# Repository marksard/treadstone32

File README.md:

# treadstone32
A 32-key compact keyboard project.  

This repository contains projects from rev2 onward. rev1, lite related projects can be found at the following links.  
[https://github.com/marksard/Keyboards/tree/master](https://github.com/marksard/Keyboards/tree/master)

# Completed example

# Layout

# Support software

QMK Firmware  
https://github.com/marksard/qmk_firmware/tree/own_build/keyboards/marksard/treadstone32/rev2

# Build guide

https://github.com/marksard/treadstone32/blob/main/documents/buildguide.md

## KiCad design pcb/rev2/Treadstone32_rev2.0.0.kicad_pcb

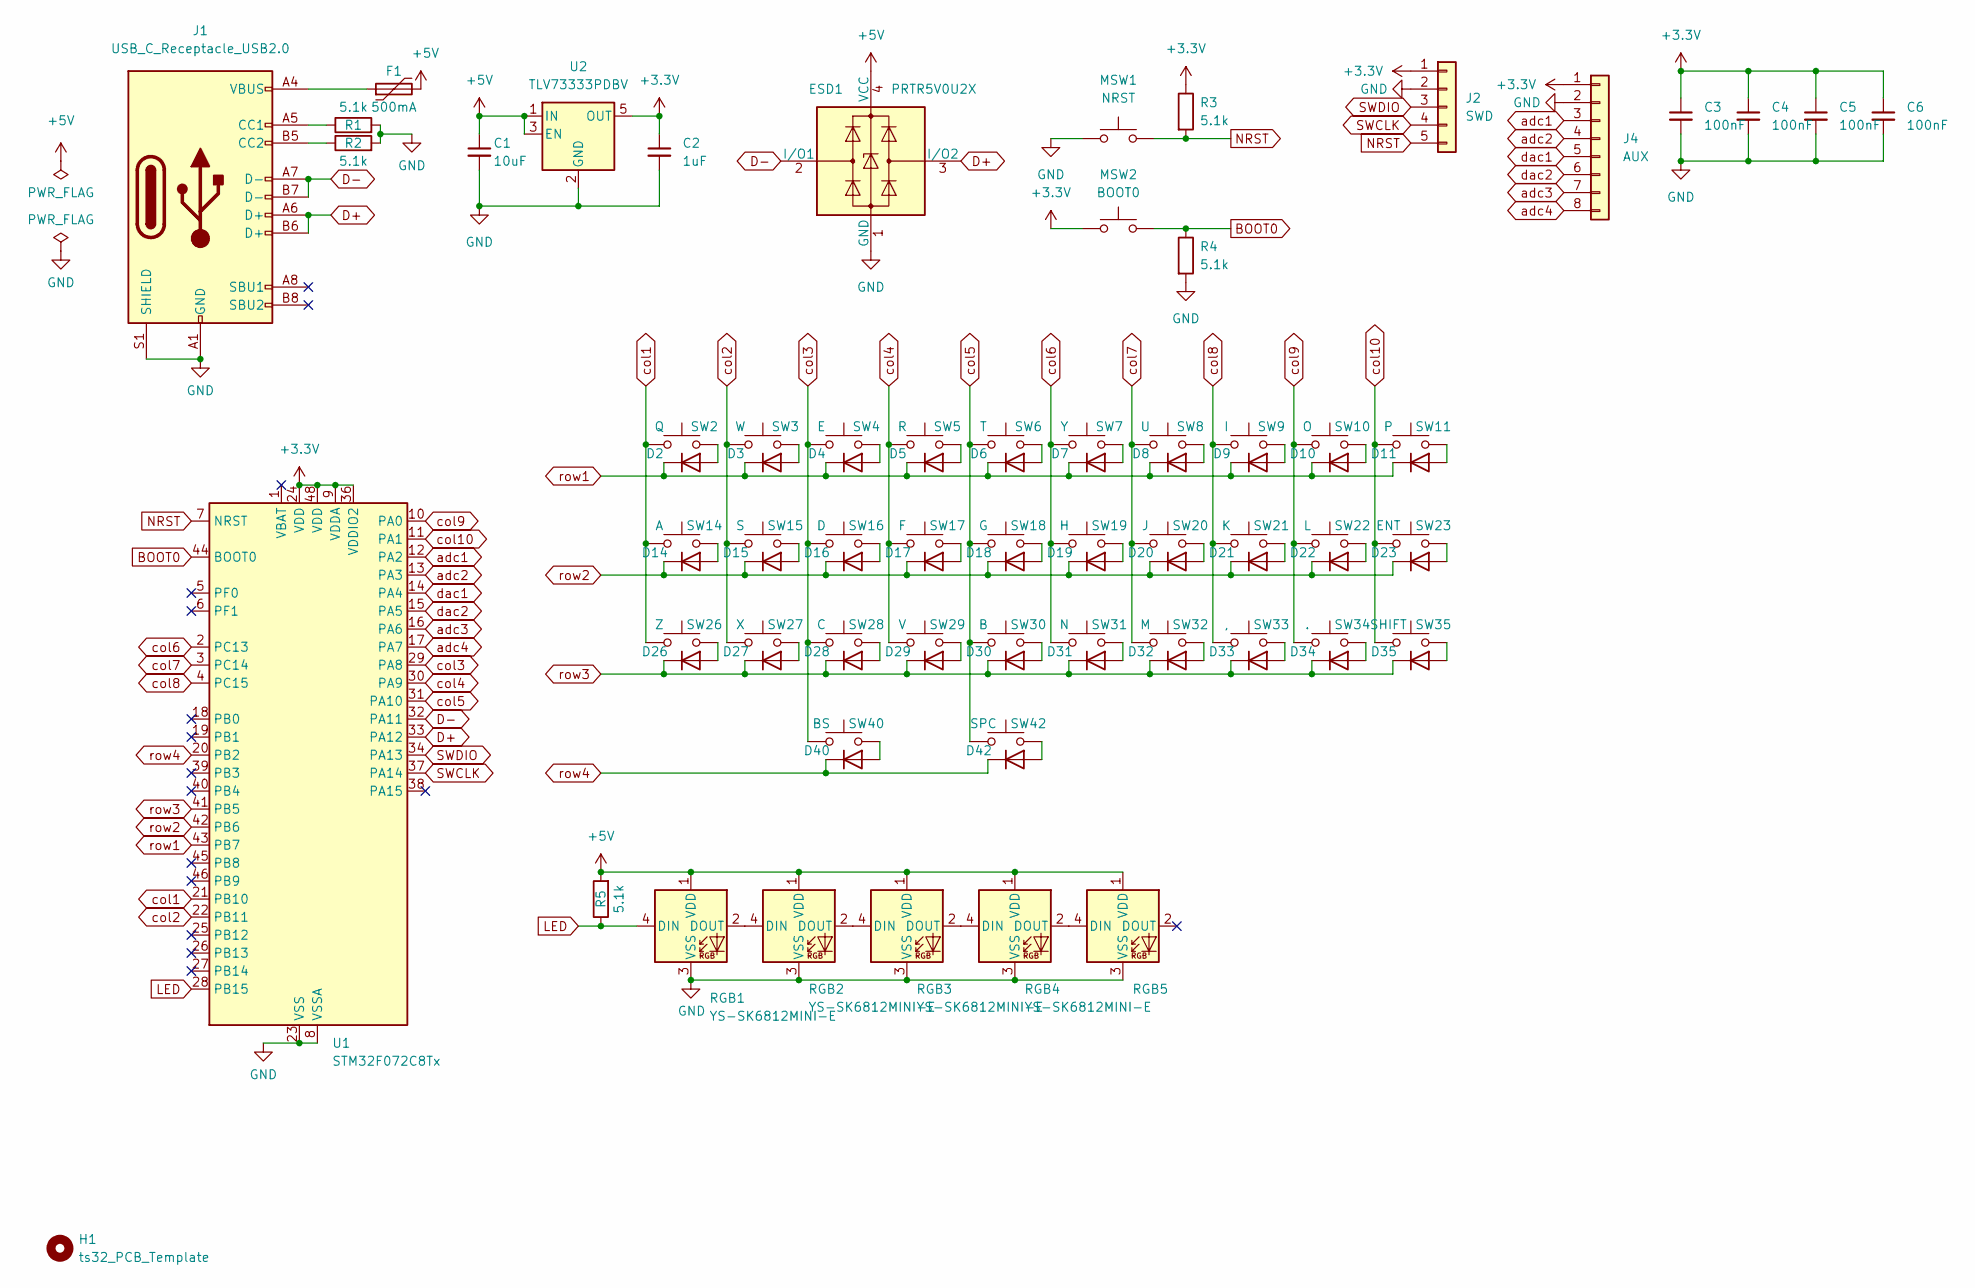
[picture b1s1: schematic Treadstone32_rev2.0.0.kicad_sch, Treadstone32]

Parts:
C1: 10uF; C_0603_1608Metric; LCSC C19702
C2: 1uF; C_0402_1005Metric; LCSC C52923
C3, C4, C5, C6: 100nF; C_0402_1005Metric; LCSC C1525
D2, D3, D4, D5, D6, D7, D8, D9, D10, D11, D14, D15, D16, D17, D18, D19, D20, D21, D22, D23, D26, D27, D28, D29, D30, D31, D32, D33, D34, D35, D40, D42: D; D_SOD-123; LCSC C81598
ESD1: PRTR5V0U2X; SOT-143; LCSC C12333
F1: 500mA; Fuse_0805_2012Metric; LCSC C261942
H1: ts32_PCB_Template; ts32_PCB_Template_v2.0.0
J1: USB_C_Receptacle_USB2.0; HRO-TYPE-C-31-M-13x; LCSC C2848619
J2: SWD; PinHeader_1x05_P2.54mm_Vertical
J4: AUX; PinHeader_1x08_P2.54mm_Vertical
MSW1: NRST; TVBP06-B043CB
MSW2: BOOT0; TVBP06-B043CB
R1, R2: 5.1k; R_0603_1608Metric; LCSC C23186
R3, R4: 5.1k; R_0402_1005Metric; LCSC C23186
R5: 5.1k; R_0603_1608Metric; LCSC C445832
RGB1, RGB2, RGB3, RGB4, RGB5: YS-SK6812MINI-E; YS-SK6812MINI-E_undergrow; LCSC C5378731
SW2: Q; MX-Hotswap-1U_F; LCSC C5156480
SW3: W; MX-Hotswap-1U_F; LCSC C5156480
SW4: E; MX-Hotswap-1U_F; LCSC C5156480
SW5: R; MX-Hotswap-1U_F; LCSC C5156480
SW6: T; MX-Hotswap-1U_F; LCSC C5156480
SW7: Y; MX-Hotswap-1U_F; LCSC C5156480
SW8: U; MX-Hotswap-1U_F; LCSC C5156480
SW9: I; MX-Hotswap-1U_F; LCSC C5156480
SW10: O; MX-Hotswap-1U_F; LCSC C5156480
SW11: P; MX-Hotswap-1U_F; LCSC C5156480
SW14: A; MX-Hotswap-1U_F; LCSC C5156480
SW15: S; MX-Hotswap-1U_F; LCSC C5156480
SW16: D; MX-Hotswap-1U_F; LCSC C5156480
SW17: F; MX-Hotswap-1U_F; LCSC C5156480
SW18: G; MX-Hotswap-1U_F; LCSC C5156480
SW19: H; MX-Hotswap-1U_F; LCSC C5156480
SW20: J; MX-Hotswap-1U_F; LCSC C5156480
SW21: K; MX-Hotswap-1U_F; LCSC C5156480
SW22: L; MX-Hotswap-1U_F; LCSC C5156480
SW23: ENT; MX-Hotswap-1U_F; LCSC C5156480
SW26: Z; MX-Hotswap-1U_F; LCSC C5156480
SW27: X; MX-Hotswap-1U_F; LCSC C5156480
SW28: C; MX-Hotswap-1U_F; LCSC C5156480
SW29: V; MX-Hotswap-1U_F; LCSC C5156480
SW30: B; MX-Hotswap-1U_F; LCSC C5156480
SW31: N; MX-Hotswap-1U_F; LCSC C5156480
SW32: M; MX-Hotswap-1U_F; LCSC C5156480
SW33: ,; MX-Hotswap-1U_F; LCSC C5156480
SW34: .; MX-Hotswap-1U_F; LCSC C5156480
SW35: SHIFT; MX-Hotswap-1U_F; LCSC C5156480
SW40: BS; MX-Hotswap-1U_F; LCSC C5156480
SW42: SPC; MX-Hotswap-1U_F; LCSC C5156480
U1: STM32F072C8Tx; LQFP-48_7x7mm_P0.5mm; LCSC C80488
U2: TLV73333PDBV; SOT-23-5; LCSC C134139

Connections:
+3.3V: C2.1, C3.1, C4.1, C5.1, C6.1, J2.1, J4.1, MSW2.1, R3.1, U1.9 (VDDA), U1.24 (VDD), U1.36 (VDDIO2), U1.48 (VDD), U2.5 (OUT)
+5V: C1.1, ESD1.4 (VCC), F1.2, R5.2, U2.1 (IN), U2.3 (EN); also elsewhere on the board
BOOT0: MSW2.2, R4.1, U1.44 (BOOT0)
D+: ESD1.3 (I/O2), J1.A6 (D+), J1.B6 (D+), U1.33 (PA12)
D-: ESD1.2 (I/O1), J1.A7 (D-), J1.B7 (D-), U1.32 (PA11)
GND: C1.2, C2.2, C3.2, C4.2, C5.2, C6.2, ESD1.1 (GND), J1.A1 (GND), J1.A12 (GND), J1.B1 (GND), J1.B12 (GND), J1.S1 (SHIELD), J2.2, J4.2, MSW1.1, R1.2, R2.2, R4.2, U1.8 (VSSA), U1.23 (VSS), U1.35 (VSS), U1.47 (VSS), U2.2 (GND); also elsewhere on the board
LED: R5.1, U1.28 (PB15); also elsewhere on the board
NRST: J2.5, MSW1.2, R3.2, U1.7 (NRST)
unnamed: D2.2 (A), SW2.2
unnamed: D3.2 (A), SW3.2
unnamed: D4.2 (A), SW4.2
unnamed: D5.2 (A), SW5.2
unnamed: D6.2 (A), SW6.2
unnamed: D7.2 (A), SW7.2
unnamed: D8.2 (A), SW8.2
unnamed: D9.2 (A), SW9.2
unnamed: D10.2 (A), SW10.2
unnamed: D11.2 (A), SW11.2
unnamed: D14.2 (A), SW14.2
unnamed: D15.2 (A), SW15.2
unnamed: D16.2 (A), SW16.2
unnamed: D17.2 (A), SW17.2
unnamed: D18.2 (A), SW18.2
unnamed: D19.2 (A), SW19.2
unnamed: D20.2 (A), SW20.2
unnamed: D21.2 (A), SW21.2
unnamed: D22.2 (A), SW22.2
unnamed: D23.2 (A), SW23.2
unnamed: D26.2 (A), SW26.2
unnamed: D27.2 (A), SW27.2
unnamed: D28.2 (A), SW28.2
unnamed: D29.2 (A), SW29.2
unnamed: D30.2 (A), SW30.2
unnamed: D31.2 (A), SW31.2
unnamed: D32.2 (A), SW32.2
unnamed: D33.2 (A), SW33.2
unnamed: D34.2 (A), SW34.2
unnamed: D35.2 (A), SW35.2
unnamed: D40.2 (A), SW40.2
unnamed: D42.2 (A), SW42.2
unnamed: F1.1, J1.A4 (VBUS), J1.A9 (VBUS), J1.B4 (VBUS), J1.B9 (VBUS)
unnamed: J1.A5 (CC1), R1.1
unnamed: J1.B5 (CC2), R2.1
SWCLK: J2.4, U1.37 (PA14)
SWDIO: J2.3, U1.34 (PA13)
adc1: J4.3, U1.12 (PA2)
adc2: J4.4, U1.13 (PA3)
adc3: J4.7, U1.16 (PA6)
adc4: J4.8, U1.17 (PA7)
col1: SW2.1, SW14.1, SW26.1, U1.21 (PB10)
col2: SW3.1, SW15.1, SW27.1, U1.22 (PB11)
col3: SW4.1, SW16.1, SW28.1, SW40.1, U1.29 (PA8)
col4: SW5.1, SW17.1, SW29.1, U1.30 (PA9)
col5: SW6.1, SW18.1, SW30.1, SW42.1, U1.31 (PA10)
col6: SW7.1, SW19.1, SW31.1, U1.2 (PC13)
col7: SW8.1, SW20.1, SW32.1, U1.3 (PC14)
col8: SW9.1, SW21.1, SW33.1, U1.4 (PC15)
col9: SW10.1, SW22.1, SW34.1, U1.10 (PA0)
col10: SW11.1, SW23.1, SW35.1, U1.11 (PA1)
dac1: J4.5, U1.14 (PA4)
dac2: J4.6, U1.15 (PA5)
row1: D2.1 (K), D3.1 (K), D4.1 (K), D5.1 (K), D6.1 (K), D7.1 (K), D8.1 (K), D9.1 (K), D10.1 (K), D11.1 (K), U1.43 (PB7)
row2: D14.1 (K), D15.1 (K), D16.1 (K), D17.1 (K), D18.1 (K), D19.1 (K), D20.1 (K), D21.1 (K), D22.1 (K), D23.1 (K), U1.42 (PB6)
row3: D26.1 (K), D27.1 (K), D28.1 (K), D29.1 (K), D30.1 (K), D31.1 (K), D32.1 (K), D33.1 (K), D34.1 (K), D35.1 (K), U1.41 (PB5)
row4: D40.1 (K), D42.1 (K), U1.20 (PB2)

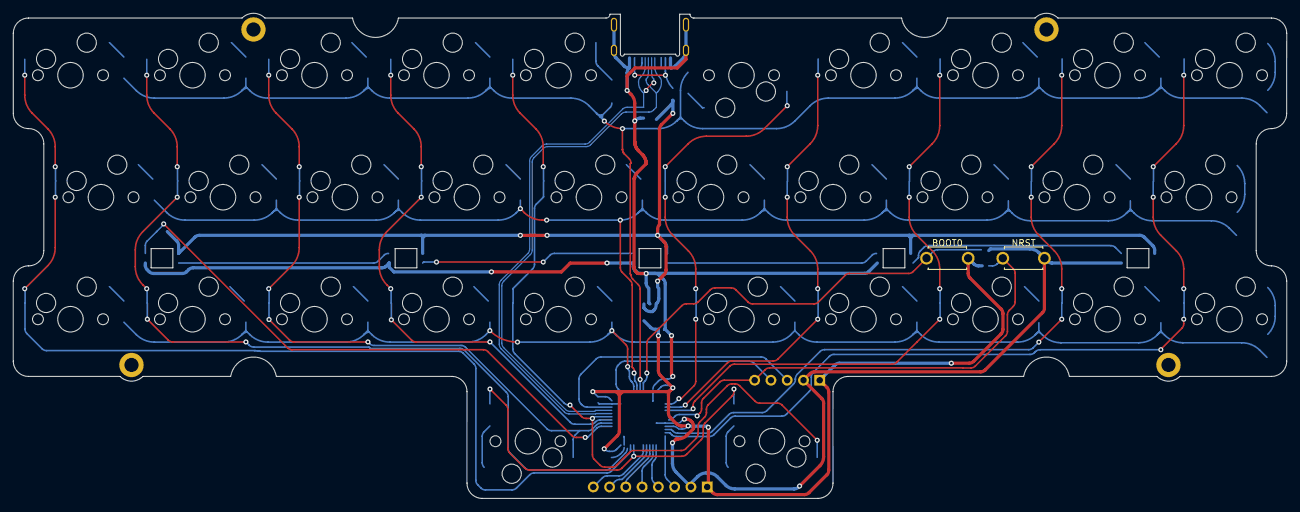
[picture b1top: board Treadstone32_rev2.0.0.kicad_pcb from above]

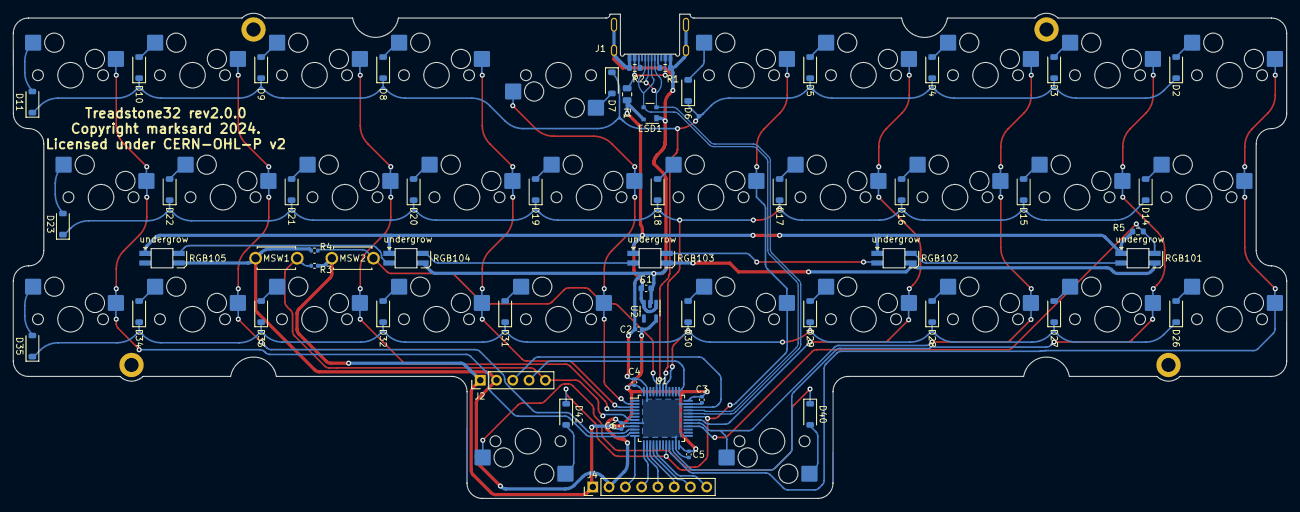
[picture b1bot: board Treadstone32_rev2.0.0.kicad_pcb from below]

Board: 2 copper layers, 198.8 x 75.8 mm, 90 parts (89 on the bottom side), 69 nets.

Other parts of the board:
RGB101, RGB102, RGB103, RGB104, RGB105: YS-SK6812MINI-E; YS-SK6812MINI-E_undergrow

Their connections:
+5V: RGB101.1 (VDD), RGB102.1 (VDD), RGB103.1 (VDD), RGB104.1 (VDD), RGB105.1 (VDD); also elsewhere on the board
GND: RGB101.3 (VSS), RGB102.3 (VSS), RGB103.3 (VSS), RGB104.3 (VSS), RGB105.3 (VSS); also elsewhere on the board
LED: RGB101.4 (DIN); also elsewhere on the board
unnamed: RGB101.2 (DOUT), RGB102.4 (DIN)
unnamed: RGB102.2 (DOUT), RGB103.4 (DIN)
unnamed: RGB103.2 (DOUT), RGB104.4 (DIN)
unnamed: RGB104.2 (DOUT), RGB105.4 (DIN)

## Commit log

2024-01-20 Create LICENSE
2024-01-30 add pcb files
2024-02-29 Add buildguide

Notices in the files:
pcb/rev2/Treadstone32_rev2.0.0.kicad_pcb:
Licensed under CERN-OHL-P v2
